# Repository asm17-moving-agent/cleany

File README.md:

# Cleany 로봇 런타임

Cleany 로봇의 ROS 2 runtime, Gazebo/MuJoCo 시뮬레이션, ESP32 펌웨어를 관리하는 저장소입니다. 제품 목표와 설계 결정은 [KB](docs/cleany-docs/README.md)에서 확인합니다. 각 구현과 시험의 상태는 제품 전체의 완료 여부와 구분합니다.

## 문서 지도

```mermaid
flowchart TB
    KB["KB / 제품 목표와 설계 결정"]
    Entry["README / 작업 선택"]
    Setup["DEVELOPMENT_SETUP / 환경과 빌드"]
    Run["RUNNING / 실행"]
    Test["TESTING / 검증"]
    Cal["CALIBRATION / 수집과 평가"]
    Contract["INTEGRATION / 연결과 계약 위치"]
    Ref["코드 옆 docs / 단위와 안전 규약"]
    API["ROS_INTERFACES / 노드별 통신 목록"]
    Evidence["EVIDENCE / 과거 원본 위치"]
    KB -. "제품 기준" .-> Entry
    Entry --> Setup
    Setup --> Run
    Run --> Test
    Run --> Cal
    Entry --> Contract
    Contract --> Ref
    Entry --> API
    API --> Ref
    Test --> Evidence
```

## 개발 시작

기준 환경은 Ubuntu 22.04, ROS 2 Humble, Python 3.10, Gazebo Fortress 6입니다. 새 환경은 [개발환경 설치](docs/DEVELOPMENT_SETUP.md)를 먼저 따릅니다. 아래 명령은 저장소 루트의 Humble 터미널에서 실행합니다.

```bash
git submodule update --init --recursive docs/cleany-docs
source /opt/ros/humble/setup.bash
make deps-gazebo
make test-gazebo
make sim-gazebo
```

전체 workspace는 `make deps`, `make build`, `make test`를 사용합니다. 각 검사의 범위와 시뮬레이션, 실물 검증의 차이는 [테스트 가이드](docs/TESTING.md)에서 확인합니다.

## 필요한 문서

| 작업 | 문서 |
|---|---|
| 환경 설치, 의존성, 빌드 경로 | [개발환경](docs/DEVELOPMENT_SETUP.md) |
| 시뮬레이션, Mission Runtime, Monitor 실행 | [실행](docs/RUNNING.md) |
| 변경 검증, runtime 시험, 결과 저장 | [테스트](docs/TESTING.md) |
| hand-eye 데이터 수집과 검토 | [Calibration](docs/CALIBRATION.md) |
| 노드별 토픽, 서비스, 액션 찾기 | [ROS 인터페이스 색인](docs/ROS_INTERFACES.md) |
| Backend, ROS, MCU 연동 | [연동과 계약](docs/INTEGRATION.md) |
| 펌웨어 빌드, 업로드, 장치 확인 | [ESP32](esp32/README.md), [배선](esp32/PINMAP.md) |
| 과거 보고서와 실행 원본 찾기 | [근거 색인](docs/EVIDENCE.md) |
| 코드 구조와 구현 학습 | [학습 가이드와 HTML 생성 안내](docs/guide/README.md) |
| 인식과 sorting 실행 | [Perception](ros2_ws/src/cleany_perception/docs/runtime.md), [Manipulation](ros2_ws/src/cleany_skill_executor/docs/manipulation.md) |
| 물체 하나의 Action 실행 | [Mock 서버](ros2_ws/src/cleany_skill_executor/docs/manipulation_mock_usage.md), [MuJoCo BT 서버](ros2_ws/src/cleany_manipulation_bt/README.md) |
| 제품, 설계, 미해결 질문 | [KB](docs/cleany-docs/README.md) |

## 코드 위치

| 위치 | 책임 |
|---|---|
| `ros2_ws/src/` | ROS 패키지, 순수 core, launch와 package 설정 |
| `esp32/` | micro-ROS 펌웨어, 빌드 보조 도구, 장치 없는 검사와 PCB |
| `tests/` | 패키지 경계를 넘는 통합 검사 |
| `tools/` | 빌드 출력 정리와 vision 환경 준비 도구 |

생성물과 실행 원본은 기본적으로 worktree 옆 `../cleany-data/`에 둡니다. 사용 가능한 명령은 `make help`, 실제 옵션은 Makefile, launch, config에서 확인합니다. 문서 변경은 기존 설명에 반영하며, README에는 날짜별 구현 일지를 추가하지 않습니다.

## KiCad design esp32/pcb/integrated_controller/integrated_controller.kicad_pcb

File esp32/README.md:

# ESP32-S3 micro-ROS motor controller

Native USB micro-ROS와 encoder, PWM/DIR로 4륜을 제어하는 펌웨어입니다. Target은 ESP32-S3 N32R16V(octal flash 32 MB / PSRAM 16 MB), PlatformIO environment는 `esp32-s3-microros`입니다. GPIO는 [PINMAP](PINMAP.md), 고정 버전은 `micro_ros.lock.json`에서 확인합니다.

| 경로 | 역할 |
|---|---|
| src/ | firmware, motor core |
| host_tests/ | 장치 없는 C++/Python 검사 |
| scripts/ | PlatformIO, 고정 dependency bootstrap |
| microros_smoke/ | micro-ROS/type-support 링크 검사 |
| imu_calibration/ | MPU6050 정지 보정 진단과 USB JSON 결과 |
| pcb/ | KiCad, 로컬 library |
| micro_ros/, .venv/ | 생성 dependency, 빌드 도구 |

도구 이동 후에는 `make firmware-setup`으로 Git wrapper 링크를 갱신합니다. Wrapper는 component root와 하위 폴더 clone 모두 revision을 고정합니다.

## KiCad 보드

[통합 컨트롤러 프로젝트](pcb/integrated_controller/integrated_controller.kicad_pro)는
ESP32-S3 모듈, BNO055, ToF 멀티플렉서와 전원 회로를 포함합니다.
KiCad 10에서 프로젝트를 열고 [보드 핀맵](pcb/integrated_controller/PINMAP.md),
[BOM](pcb/integrated_controller/BOM.md), [제작 규칙](pcb/integrated_controller/DESIGN_RULES.md)을 함께 확인합니다.
검사는 저장소 루트의 `make test-pcb`로 실행하며 환경과 결과 경로는
[개발환경](../docs/DEVELOPMENT_SETUP.md#kicad-pcb-검증-환경)과
[검증 절차](../docs/TESTING.md#통합-컨트롤러-pcb-검증)를 따릅니다.

현재 펌웨어의 모터 GPIO와 MPU6050 드라이버는 기존 모터 보드 기준입니다.
통합 보드에는 모터 GPIO 매핑과 BNO055 드라이버의 별도 이식이 필요합니다.
[별도 USB 센서 캐리어](pcb/sensor_controller/sensor_controller.md)는
회로도와 제작 설정 초안이며 부품 배치와 배선이 없는 상태입니다.

## ROS 인터페이스

노드 이름은 `cleany_motor_controller`, namespace는 기본 root입니다. [main.cpp](src/main.cpp)의 rclc entity 초기화를 기준으로 기록합니다.

| 종류 / 방향 | 기본 이름 | ROS 타입 | QoS와 주기 |
|---|---|---|---|
| 토픽 구독 | `base/wheel_command` | `cleany_base_interfaces/msg/WheelCommand` | Best-effort, volatile, keep-last 1 |
| 토픽 발행 | `base/wheel_state` | `cleany_base_interfaces/msg/WheelState` | Best-effort, volatile, keep-last 1; 50 Hz |
| 토픽 발행 | `base/imu_state` | `cleany_base_interfaces/msg/ImuState` | Best-effort, volatile, keep-last 1; 최대 100 Hz |

MCU에 서비스와 액션은 없습니다. 구동 허가는 WheelCommand의 ENABLE/STOP으로 처리하고, ROS `base/enable` 서비스는 [base driver](../ros2_ws/src/cleany_base_driver/docs/interfaces.md)가 제공합니다. 전체 노드는 [ROS 인터페이스 색인](../docs/ROS_INTERFACES.md)에서 찾습니다.

## Runtime

```mermaid
flowchart TB
    Driver["ROS base driver"] -->|"base/wheel_command"| USB["USB XRCE-DDS"]
    subgraph Communication["통신 task"]
        Callback["rclc callback"] --> Mailbox["최신 명령 mailbox"]
        Ping["Agent ping / 재연결"]
    end
    USB --> Callback
    subgraph Control["motor task / 5 ms"]
        Gate["ENABLE / deadline 검사"] --> PI["PI + feed-forward"] --> PWM["PWM / DIR"]
        Encoder["Encoder feedback"] --> PI
        Encoder --> State["Wheel state"]
    end
    Mailbox --> Gate
    Ping -->|"단절 시 STOP latch"| Gate
    PWM --> Motor["네 휠"]
    Motor --> Encoder
    State -->|"base/wheel_state"| USB
    USB --> Driver
```

통신 task는 USB, ROS entity, Agent 재연결을 관리합니다. Motor task는 독립적으로 5 ms마다 실행하며, `motorMutex` 안에서 명령을 검사하고 PWM을 갱신합니다. 부팅 시 PWM은 0이고 구동은 disabled입니다. Zero ENABLE을 받은 뒤 VELOCITY를 허용합니다.

| 조건 | 처리 |
|---|---|
| STOP, 재연결 | Sequence high-water 유지 |
| 거부된 명령, 반복 ENABLE | Deadline과 이동 목표를 갱신하지 않음 |
| STOP latch | 대기 명령 삭제; 새 sequence로 오래된 ENABLE 차단 |
| Deadline | 수신 후 최대 250 ms; 명령 처리 전에 검사 |
| 만료, 단절 | 허가 해제; 재개에는 새 ENABLE 필요 |
| STOP, 만료, 단절 | Controller reset과 PWM 0 요청 |
| Agent ping 실패 | STOP latch → entity teardown → 재연결 |

| 항목 | 값과 규칙 |
|---|---|
| Wheel ceiling, 목표 반올림 | 10 rad/s, 0.1 rad/s 단위 |
| PWM | 20 kHz, 명령 슬루는 20 ms당 가속 1%p, 감속 3%p |
| 방향 반전 | 측정 속도 ≤0.5 rad/s를 50 ms 유지한 뒤 DIR 변경 |
| Wheel 배열 | FL/FR/RL/RR → PCB M1/M2/M4/M3, mapping `{0,1,3,2}` |
| 극성, encoder | 극성은 MCU에서만 적용; 출력축 1회전=3172 counts |
| State | 50 Hz, best-effort/volatile/keep-last-1 |
| MCU 시간, Boot ID | Monotonic µs; reboot baseline 식별 |
| USB | Agent용 framed XRCE-DDS 전용 |
| Agent ping | 100 ms 주기, 20 ms timeout |

메시지와 명령 수락 규칙은 [protocol v2](../ros2_ws/src/cleany_base_interfaces/docs/protocol.md)를 따릅니다.

## Runtime MPU6050 telemetry

The motor image also acquires MPU6050 data on J_I2C1 (SDA GPIO41, SCL GPIO42),
using the existing driver: 100 kHz I2C, 100 Hz sensor sampling, ±250 deg/s gyro,
±2 g accelerometer and 42 Hz gyro DLPF. Module/external I2C pull-ups are required.

The independent priority-2 acquisition task polls data-ready every 2 ms. It does
not take `motorMutex`. The priority-6 motor and priority-4 communication tasks
remain separate. A one-entry overwrite queue drops intermediate data if
communication stalls; reconnect does not drain a sample backlog.

The communication task publishes fixed-size `ImuState` on `base/imu_state`,
best effort / volatile / keep last 1, driven by newly acquired samples up to
the sensor rate. WheelState remains at 50 Hz. Actual rates and motor timing
under combined USB/I2C load require robot measurements.

Packets carry uncalibrated sensor-frame SI vectors, temperature, MCU MAC,
WHO_AM_I, boot ID, packet sequence, MCU acquisition timestamp and fault bits.
ImuState v2 also carries MCU-corrected gyro, the selected bias/covariance,
and calibration state/reason. Build the ROS interfaces and firmware together.
Acquisitions older than 100 ms and duplicate/backward timestamps are not sent
as new measurements. Missing/error data produces a sensor-fault heartbeat
at most 10 Hz; saturation has its own fault bit. Initialization/read errors
retry with 250 ms to 5 s backoff. IMU I2C failure does not authorize motors.

### Power-on calibration

The acquisition task calibrates once per MCU boot, independently of the Agent.
Defaults are 5 s settling, 1,000 training samples and 500 holdout samples, with
a 25 s deadline. It reuses the existing online gyro statistics. Noise/residual
failure, sensor/sample errors or timeout select the saved bench coefficients.
The selection remains fixed until MCU reboot, including across Agent reconnects.

During calibration, motor PWM stays zero, PID updates are skipped and non-STOP
commands are discarded. Completion only releases this inhibit; a fresh ENABLE
is still required. STOP, watchdog and disconnect handling remain active.
Fallback can release the calibration inhibit even if the sensor is unavailable;
sensor errors are still reported, and no angular-rate samples are fabricated.

Edit [`ros2_ws/src/cleany_base_driver/config/imu_calibration.json`](../ros2_ws/src/cleany_base_driver/config/imu_calibration.json)
to configure timing, windows, checks and measured fallback bias/covariance.
`make firmware-build` validates it and generates `cleany_config/imu_startup_config.hpp`
inside the PlatformIO build directory. The configuration is compiled into the
image; changes require rebuilding and uploading. Runtime checks samples and
observed statistics. A single acquisition-side enqueue helper attaches calibration
metadata and releases the boot inhibit on completion. The IMU task uses 6144 bytes
of stack for online statistics.

ROS topics and status are documented under
[IMU 실시간 수신](../ros2_ws/src/cleany_base_driver/docs/imu.md#imu-실시간-수신).
The standalone [diagnostic](imu_calibration/README.md) provides bench reports;
normal startup calibration is part of the motor image.

## 휠별 초기 PI와 FF

`src/main.cpp`의 `kFl/Fr/Rl/RrControllerConfig`에서 FF scale / Kp / Ki / PWM limit 순서로 설정합니다. 변경 후 rebuild와 upload가 필요합니다. FF 출력은 `target / FF scale × PWM limit`입니다.

아래 값은 2026-10-02 네 바퀴를 공중에 띄운 무부하 시험에서 얻었습니다. PI를 끄고 네 휠을 동시에 정, 역방향으로 PWM 0→100%, 5% 간격, 1.5초씩 측정했습니다.

| 휠 | FF scale (rad/s) | Kp | Ki | PWM 상한 (%) |
|---|---:|---:|---:|---:|
| FL | 12.4261 | 4.655 | 9.309 | 100 |
| FR | 12.1178 | 4.711 | 9.421 | 100 |
| RL | 11.6403 | 4.864 | 9.728 | 100 |
| RR | 11.8128 | 4.783 | 9.566 | 100 |

FF는 `PWM≈k×속도`, `FF scale=100/k`로 추정하고 마찰 잔차는 PI로 보정했습니다. PI 추정에는 gain K, 시정수 τ, delay L과 기존 50 ms 속도 필터를 포함했습니다. 계산식은 `Kp=clamp(0.6/K,2,8)`, `Ki=Kp/max(0.5,4(τ+L))`입니다.

보정값을 업로드한 뒤 네 바퀴 동시 정·역방향 **0.5, 2, 5, 10 rad/s** 명령을
각각 5초 동안 검증했다. 마지막 0.5초 평균 속도 오차는 모든 휠에서 4.5% 이내였다.
최종 상태는 구동 비허가, PWM 0, fault 0이다.

### 2026-10-13 지면 하중 실측 캘리브레이션 및 필터 고도화

현재 `src/main.cpp`는 전후이동과 횡이동의 지면 하중 시험에서 도출한 다음
휠별 설정을 사용한다. 진단 기준값은
[`controller_baseline.json`](../tools/wheel_calibration/controller_baseline.json)에
같은 값으로 보존하며, 관련 테스트가 펌웨어 설정과의 일치를 확인한다.

| 휠 | FF scale (rad/s) | Kp | Ki | PWM 상한 (%) | 주요 지면 보정 특성 |
|---|---:|---:|---:|---:|---|
| FL | 11.9352 | 6.058 | 12.118 | 100 | 전후/횡이동 균형 최적화 |
| FR | 12.2596 | 6.030 | 12.058 | 100 | 고효율 FR 휠 출력 과다 방지 |
| RL | 11.7678 | 6.246 | 12.492 | 100 | 후륜 지지 강성 보강 |
| RR | 11.3872 | 6.154 | 12.309 | 100 | 기어박스 마찰 하중 보상 (Yaw 편주 억제) |

명령 슬루는 가속 시 20 ms당 1%, 감속 시 20 ms당 3%로 설정한다.
속도 피드백 LPF 시상수는 `kVelocityFilterTimeConstantSeconds = 0.02`초다.
STOP, 만료 및 연결 단절은 슬루 감속을 기다리지 않고 PWM zero를 요청한다.

측정과 재검증 방법은 [휠 진단 안내](../tools/wheel_calibration/README.md)와
[오도메트리 평가 안내](../tools/odometry_evaluation/README.md)를 따른다.
오도메트리 내부 제어 잔차와 바닥 테이프 또는 LiDAR 기준의 실측 오차는
별도 지표로 기록한다. 측정 JSON과 PNG는 Git 제외 경로인 `artifacts/`에 저장한다.

## 1. 빌드와 장치 없는 검사

명령은 저장소 루트에서 실행합니다. 호스트 호출 시 Ubuntu 22.04 `ros2-humble` Distrobox를 사용합니다.

```bash
make firmware-setup
make test-micro-ros-setup test-motor-core
make firmware-smoke
make firmware-build
make build-base test-base
make micro-ros-agent-build
```

Type support 원본은 `ros2_ws/src/cleany_base_interfaces`입니다. Smoke/runtime은 cache를 공유하므로 순차 빌드하며, interface, metadata, 환경을 변경하면 type support를 재생성합니다.

`cmake/microros_python.cmake` exposes the pinned generator modules to IDF's
Python during CMake configuration. PlatformIO clears the process `PYTHONPATH`
before this step, so the SCons environment alone does not cover a fresh
micro-ROS/type-support rebuild. Runtime and smoke projects share this helper.

Smoke and runtime share a library cache and build sequentially. Changes to
interfaces, metadata, or build environment regenerate type support.
`sdkconfig.defaults` configures octal memory, a 1000 Hz FreeRTOS tick, and the
USB transport. The DOUT image header lets the bootloader enable OPI.

For clangd, run inside Distrobox:

```bash
esp32/.venv/bin/platformio run -d esp32 -e esp32-s3-microros -t compiledb
```

## 2. Upload와 통신

For stationary gyro calibration on `J_I2C1`, use the separate
[MPU6050 calibration diagnostic](imu_calibration/README.md).
It provides a calibration-only image, retained USB results, measured-limit
configuration, and the motor-firmware restoration procedure.

Select the device and confirm upload:

```bash
make firmware-upload CLEANY_ESP_PORT=/dev/serial/by-id/<device> CONFIRM_UPLOAD=1
```

Agent/ROS overlay를 적용하고 DDS domain 0에서 통신을 확인합니다.

```bash
source /opt/ros/humble/setup.bash
source esp32/micro_ros/agent/install/local_setup.bash
source "$(make -s print-install-base)/local_setup.bash"
export ROS_DOMAIN_ID=0
ros2 run micro_ros_agent micro_ros_agent serial --dev "$CLEANY_ESP_PORT" -b 115200
# Another terminal with the same overlays/domain:
ros2 topic echo /base/wheel_state --qos-reliability best_effort
```

Bare MCU 확인 항목은 다음과 같습니다.

- Nonzero boot ID, 증가하는 sequence/timestamp
- Disabled 상태, 목표, PWM 0, fault 없음

## 3. 실물 인수

1. 감독자, 사람 없는 구역, 검토한 제한값, 접근 가능한 물리 E-stop을 준비합니다.
2. 바퀴를 띄워 startup 0, 회전 방향, encoder 부호를 확인합니다.
3. Enable 후 새 저속 명령으로 전진, 좌측, yaw, PI, PWM slew, 반전 dwell을 확인합니다.
4. STOP, 만료, driver/Agent 종료, USB 단절, MCU reboot의 정지 시간을 측정합니다.
5. 재연결 후 새 enable과 새 명령이 필요한지 확인합니다.

Odometry, TF 소유권은 [Base 계약](../ros2_ws/src/cleany_base_driver/docs/command-and-odometry.md)을 따릅니다. 결과에는 revision, 설정, 하중/바닥, 부호, 주기, 정지 시간을 기록합니다.

## KiCad

프로젝트는 [motor_controller.kicad_pro](pcb/motor_controller.kicad_pro)이며 symbol/footprint는 project-local table에 등록됩니다. Espressif 출처와 라이선스는 [libraries](pcb/libraries/README.md)에서 확인합니다.

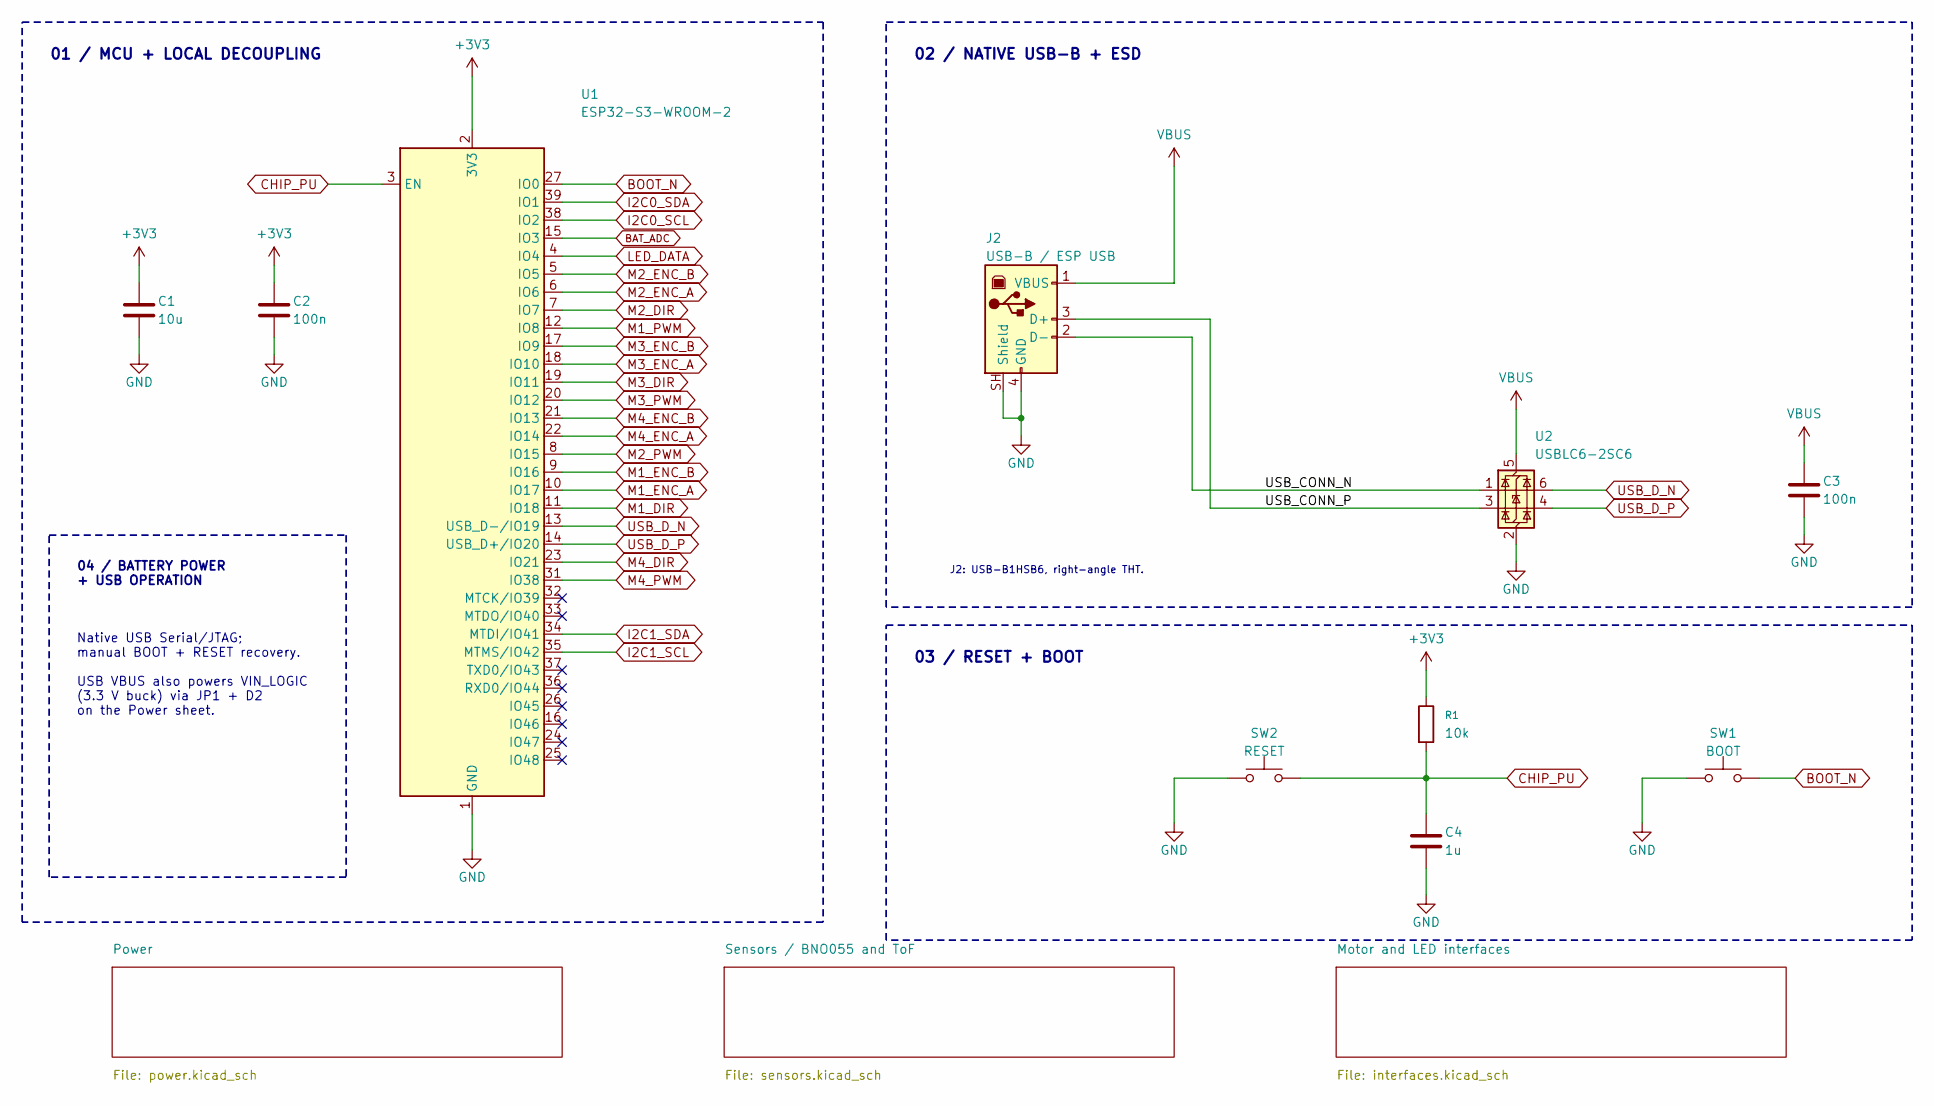
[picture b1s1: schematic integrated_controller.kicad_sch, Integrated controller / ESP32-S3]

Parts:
C1: 10u; C_0805_2012Metric; Tolerance 10%; Voltage 25V; MPN C2012X5R1E106K125DB
C2, C3: 100n; C_0603_1608Metric; Tolerance 10%; Voltage 50V; MPN C0603C104K5RACTU
C4: 1u; C_0603_1608Metric; Tolerance 10%; Voltage 16V; MPN C0603C105K4RACTU
J2: USB-B / ESP USB; USB_B_OST_USB-B1HSxx_Horizontal; MPN USB-B1HSB6
R1: 10k; R_0603_1608Metric; Tolerance 1%; MPN ERJ-3EKF1002V
SW1: BOOT; SW_SPST_PTS810; MPN PTS810SJM250SMTR LFS
SW2: RESET; SW_SPST_PTS810; MPN PTS810SJM250SMTR LFS
U1: ESP32-S3-WROOM-2; MPN ESP32-S3-WROOM-2-N32R16V
U2: USBLC6-2SC6; SOT-23-6; MPN USBLC6-2SC6

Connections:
+3V3: C1.1, C2.1, R1.1, U1.2 (3V3); also elsewhere on the board
/USB_CONN_N: J2.2 (D-), U2.1 (I/O1)
/USB_CONN_P: J2.3 (D+), U2.3 (I/O2)
BAT_ADC: U1.15 (IO3); also elsewhere on the board
BOOT_N: SW1.2, U1.27 (IO0)
CHIP_PU: C4.1, R1.2, SW2.2, U1.3 (EN)
GND: C1.2, C2.2, C3.2, C4.2, J2.4 (GND), J2.SH (Shield), SW1.1, SW2.1, U1.1 (GND), U1.40 (GND), U1.41 (GND), U2.2 (GND); also elsewhere on the board
I2C0_SCL: U1.38 (IO2); also elsewhere on the board
I2C0_SDA: U1.39 (IO1); also elsewhere on the board
I2C1_SCL: U1.35 (MTMS/IO42); also elsewhere on the board
I2C1_SDA: U1.34 (MTDI/IO41); also elsewhere on the board
LED_DATA: U1.4 (IO4); also elsewhere on the board
M1_DIR: U1.11 (IO18); also elsewhere on the board
M1_ENC_A: U1.10 (IO17); also elsewhere on the board
M1_ENC_B: U1.9 (IO16); also elsewhere on the board
M1_PWM: U1.12 (IO8); also elsewhere on the board
M2_DIR: U1.7 (IO7); also elsewhere on the board
M2_ENC_A: U1.6 (IO6); also elsewhere on the board
M2_ENC_B: U1.5 (IO5); also elsewhere on the board
M2_PWM: U1.8 (IO15); also elsewhere on the board
M3_DIR: U1.19 (IO11); also elsewhere on the board
M3_ENC_A: U1.18 (IO10); also elsewhere on the board
M3_ENC_B: U1.17 (IO9); also elsewhere on the board
M3_PWM: U1.20 (IO12); also elsewhere on the board
M4_DIR: U1.23 (IO21); also elsewhere on the board
M4_ENC_A: U1.22 (IO14); also elsewhere on the board
M4_ENC_B: U1.21 (IO13); also elsewhere on the board
M4_PWM: U1.31 (IO38); also elsewhere on the board
USB_D_N: U1.13 (USB_D-/IO19), U2.6 (I/O1)
USB_D_P: U1.14 (USB_D+/IO20), U2.4 (I/O2)
VBUS: C3.1, J2.1 (VBUS), U2.5 (VBUS); also elsewhere on the board

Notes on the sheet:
04 / BATTERY POWER + USB OPERATION
Native USB Serial/JTAG; manual BOOT + RESET recovery. USB VBUS also powers VIN_LOGIC (3.3 V buck) via JP1 + D2 on the Power sheet.
J2: USB-B1HSB6, right-angle THT.
02 / NATIVE USB-B + ESD
01 / MCU + LOCAL DECOUPLING
03 / RESET + BOOT

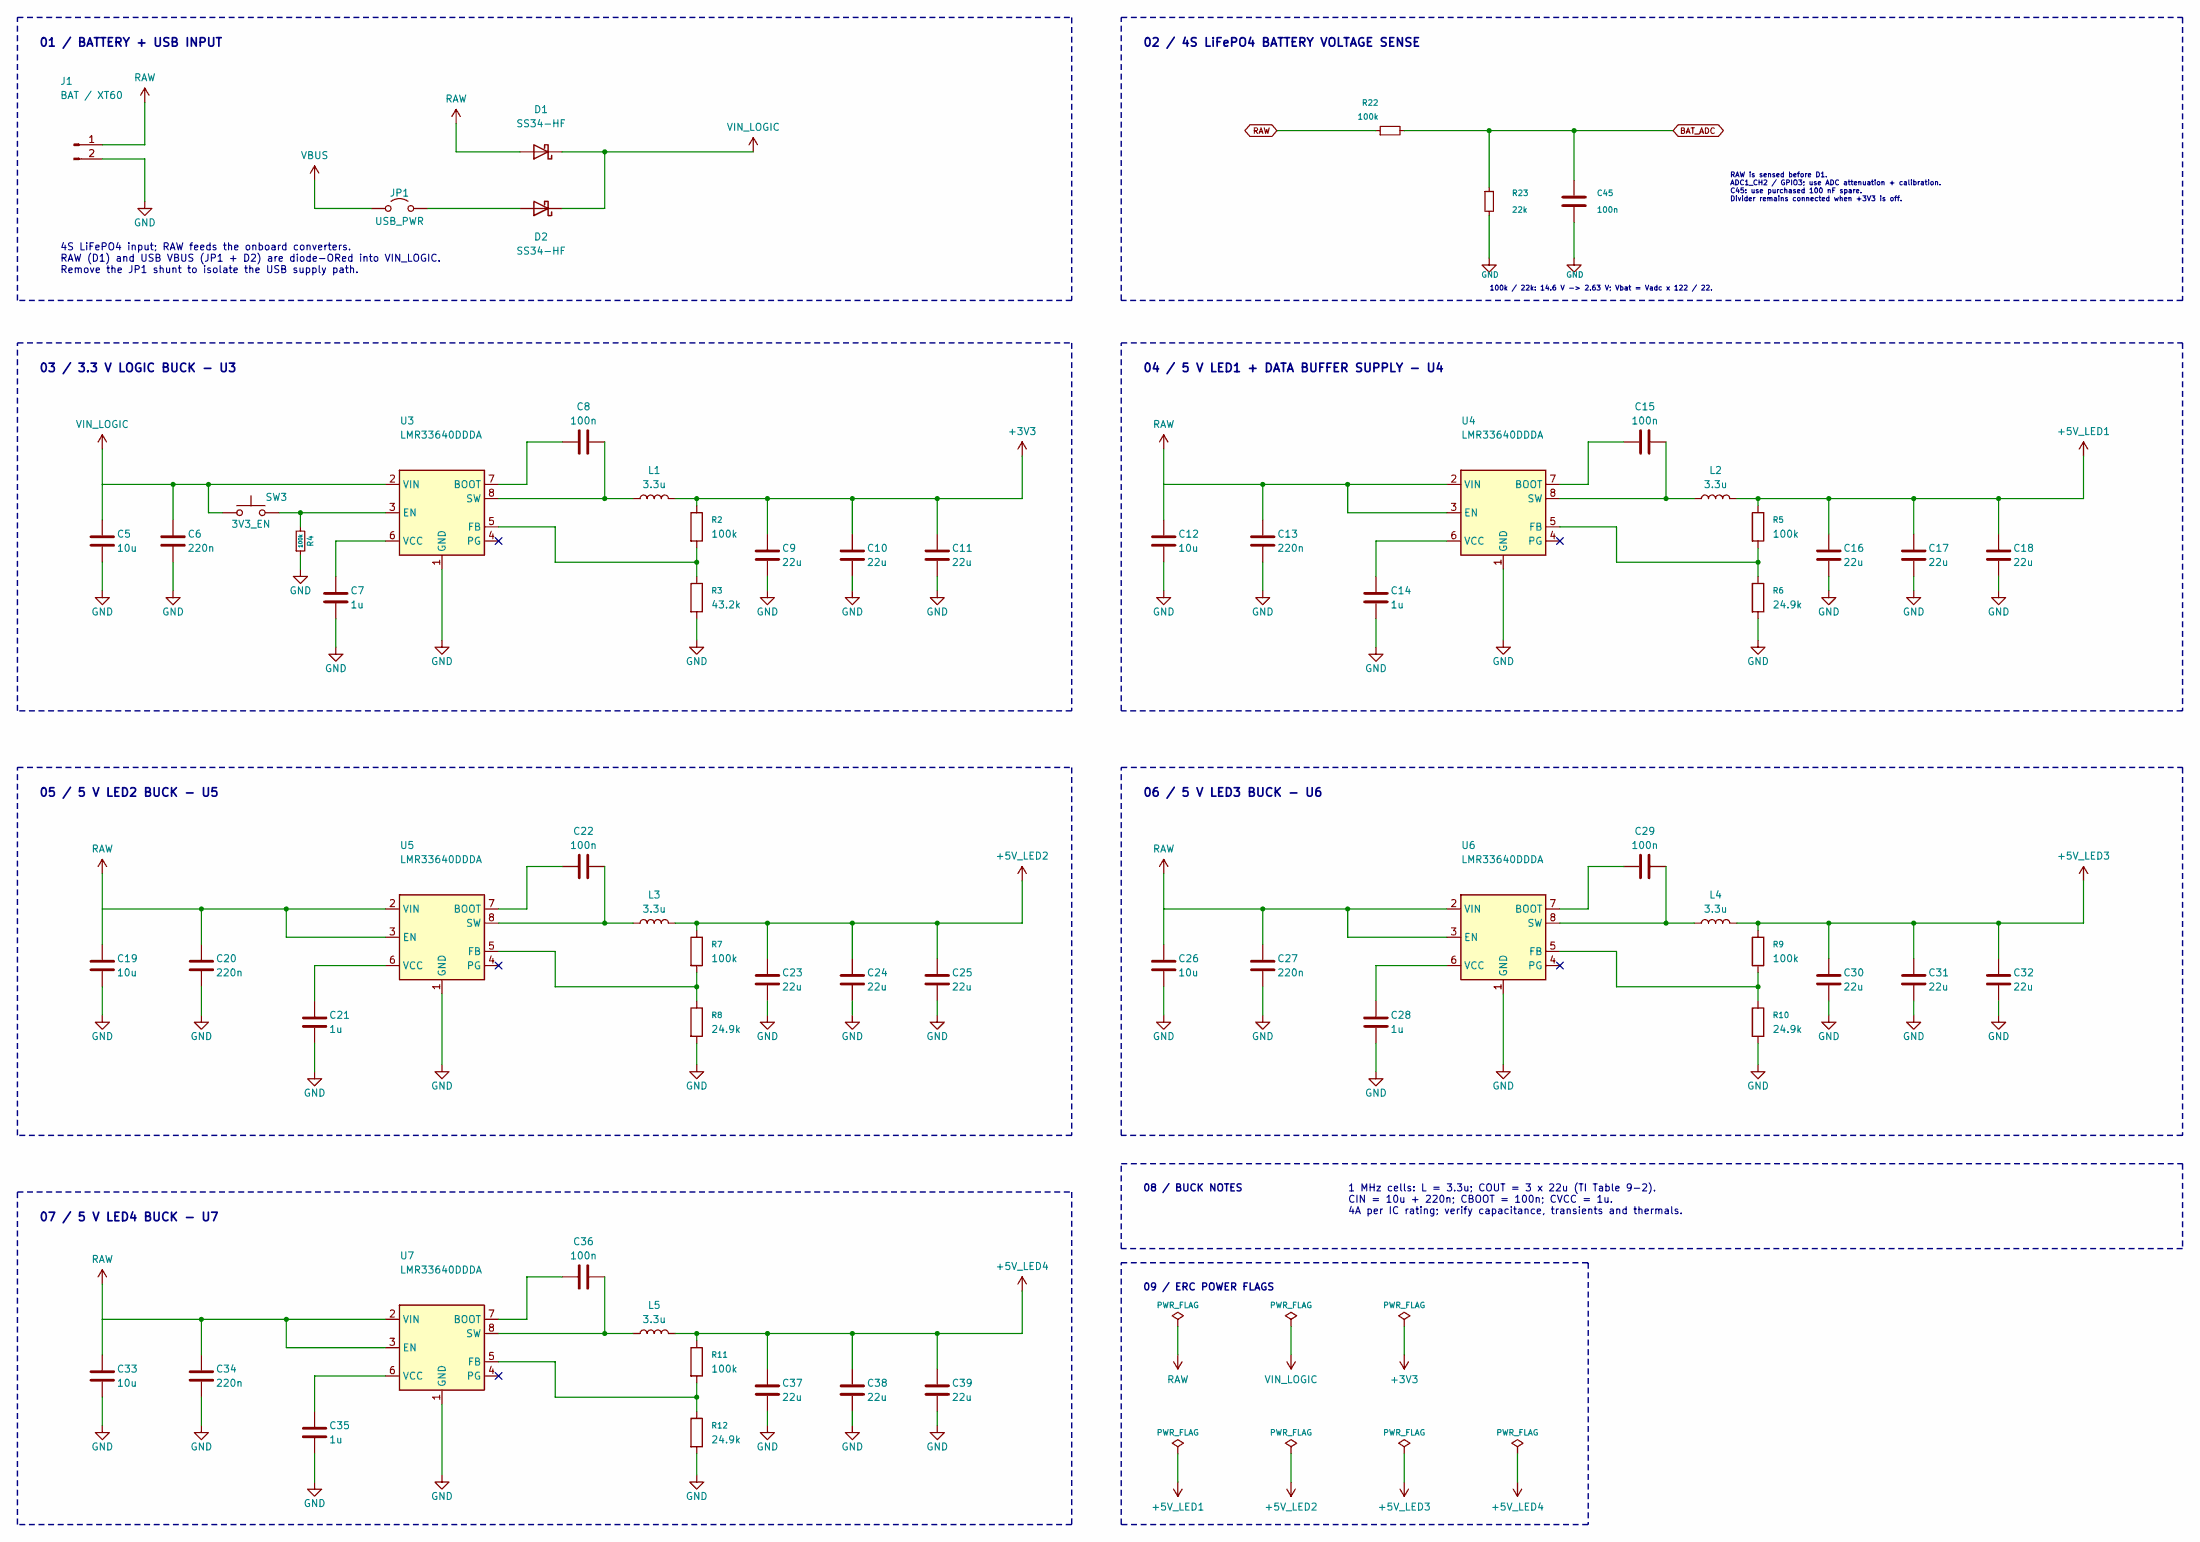
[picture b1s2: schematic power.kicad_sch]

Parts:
C5, C12, C19, C26, C33: 10u; C_1206_3216Metric; Voltage 50V; Tolerance 10%; MPN GMC31X5R106K50NT
C6, C13, C20, C27, C34: 220n; C_0603_1608Metric; Voltage 50V; Tolerance 10%; MPN GRM188R71H224KAC4D
C7, C14, C21, C28, C35: 1u; C_0603_1608Metric; Voltage 16V; Tolerance 20%; MPN CL10B105MO8NNWC
C8, C15, C22, C29, C36: 100n; C_0603_1608Metric; Voltage 25V; Tolerance 10%; MPN KGM15BR71E104KT
C9, C10, C11, C16, C17, C18, C23, C24, C25, C30, C31, C32, C37, C38, C39: 22u; C_1210_3225Metric; Voltage 16V; Tolerance 20%; MPN CGA6P1X7R1C226M250AC
C45: 100n; C_0603_1608Metric; MPN C0603C104K5RACTU
D1, D2: SS34-HF; D_SMA; MPN SS34-HF
J1: BAT / XT60; XT60_Generic_Vertical_1x02_P7.20mm_Pin1Positive
JP1: USB_PWR; PinHeader_1x02_P2.54mm_Vertical; MPN PREC002SAAN-RC
L1, L2, L3, L4, L5: 3.3u; Wuerth_74439346033_6.65x6.45mm; Tolerance 20%; MPN 74439346033
R2, R5, R7, R9, R11: 100k; R_0603_1608Metric; Tolerance 1%; MPN CRCW0603100KFKEA
R3: 43.2k; R_0603_1608Metric; Tolerance 1%; MPN ERJ-3EKF4322V
R4: 100k; R_0603_1608Metric
R6, R8, R10, R12: 24.9k; R_0603_1608Metric; Tolerance 1%; MPN RC0603FR-0724K9L
R22: 100k; R_0603_1608Metric; MPN CRCW0603100KFKEA
R23: 22k; R_0603_1608Metric; MPN CRCW060322K0FKEA
SW3: 3V3_EN; Molex_SPOX_5268-02A_1x02_P2.50mm_Horizontal
U3, U4, U5, U6, U7: LMR33640DDDA; Texas_HSOP-8-1EP_3.9x4.9mm_P1.27mm_ThermalVias; MPN LMR33640DDDAR

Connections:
+3V3: C9.1, C10.1, C11.1, L1.2, R2.1; also elsewhere on the board
+5V_LED1: C16.1, C17.1, C18.1, L2.2, R5.1; also elsewhere on the board
+5V_LED2: C23.1, C24.1, C25.1, L3.2, R7.1; also elsewhere on the board
+5V_LED3: C30.1, C31.1, C32.1, L4.2, R9.1; also elsewhere on the board
+5V_LED4: C37.1, C38.1, C39.1, L5.2, R11.1; also elsewhere on the board
BAT_ADC: C45.1, R22.2, R23.1; also elsewhere on the board
GND: C5.2, C6.2, C7.2, C9.2, C10.2, C11.2, C12.2, C13.2, C14.2, C16.2, C17.2, C18.2, C19.2, C20.2, C21.2, C23.2, C24.2, C25.2, C26.2, C27.2, C28.2, C30.2, C31.2, C32.2, C33.2, C34.2, C35.2, C37.2, C38.2, C39.2, C45.2, J1.2, R3.2, R4.1, R6.2, R8.2, R10.2, R12.2, R23.2, U3.1 (GND), U3.9 (GND), U4.1 (GND), U4.9 (GND), U5.1 (GND), U5.9 (GND), U6.1 (GND), U6.9 (GND), U7.1 (GND), U7.9 (GND); also elsewhere on the board
unnamed: D2.2 (A), JP1.2 (B)
unnamed: C8.1, U3.7 (BOOT)
unnamed: R4.2, SW3.2, U3.3 (EN)
unnamed: R2.2, R3.1, U3.5 (FB)
unnamed: C8.2, L1.1, U3.8 (SW)
unnamed: C7.1, U3.6 (VCC)
unnamed: C15.1, U4.7 (BOOT)
unnamed: R5.2, R6.1, U4.5 (FB)
unnamed: C15.2, L2.1, U4.8 (SW)
unnamed: C14.1, U4.6 (VCC)
unnamed: C22.1, U5.7 (BOOT)
unnamed: R7.2, R8.1, U5.5 (FB)
unnamed: C22.2, L3.1, U5.8 (SW)
unnamed: C21.1, U5.6 (VCC)
unnamed: C29.1, U6.7 (BOOT)
unnamed: R9.2, R10.1, U6.5 (FB)
unnamed: C29.2, L4.1, U6.8 (SW)
unnamed: C28.1, U6.6 (VCC)
unnamed: C36.1, U7.7 (BOOT)
unnamed: R11.2, R12.1, U7.5 (FB)
unnamed: C36.2, L5.1, U7.8 (SW)
unnamed: C35.1, U7.6 (VCC)
RAW: C12.1, C13.1, C19.1, C20.1, C26.1, C27.1, C33.1, C34.1, D1.2 (A), J1.1, R22.1, U4.2 (VIN), U4.3 (EN), U5.2 (VIN), U5.3 (EN), U6.2 (VIN), U6.3 (EN), U7.2 (VIN), U7.3 (EN)
VBUS: JP1.1 (A); also elsewhere on the board
VIN_LOGIC: C5.1, C6.1, D1.1 (K), D2.1 (K), SW3.1, U3.2 (VIN)

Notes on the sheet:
4S LiFePO4 input; RAW feeds the onboard converters. RAW (D1) and USB VBUS (JP1 + D2) are diode-ORed into VIN_LOGIC. Remove the JP1 shunt to isolate the USB supply path.
03 / 3.3 V LOGIC BUCK - U3
09 / ERC POWER FLAGS
07 / 5 V LED4 BUCK - U7
06 / 5 V LED3 BUCK - U6
04 / 5 V LED1 + DATA BUFFER SUPPLY - U4
08 / BUCK NOTES
05 / 5 V LED2 BUCK - U5
1 MHz cells: L = 3.3u; COUT = 3 x 22u (TI Table 9-2). CIN = 10u + 220n; CBOOT = 100n; CVCC = 1u. 4A per IC rating; verify capacitance, transients and thermals.
01 / BATTERY + USB INPUT
02 / 4S LiFePO4 BATTERY VOLTAGE SENSE
RAW is sensed before D1. ADC1_CH2 / GPIO3; use ADC attenuation + calibration. C45: use purchased 100 nF spare. Divider remains connected when +3V3 is off.
100k / 22k: 14.6 V -> 2.63 V; Vbat = Vadc x 122 / 22.

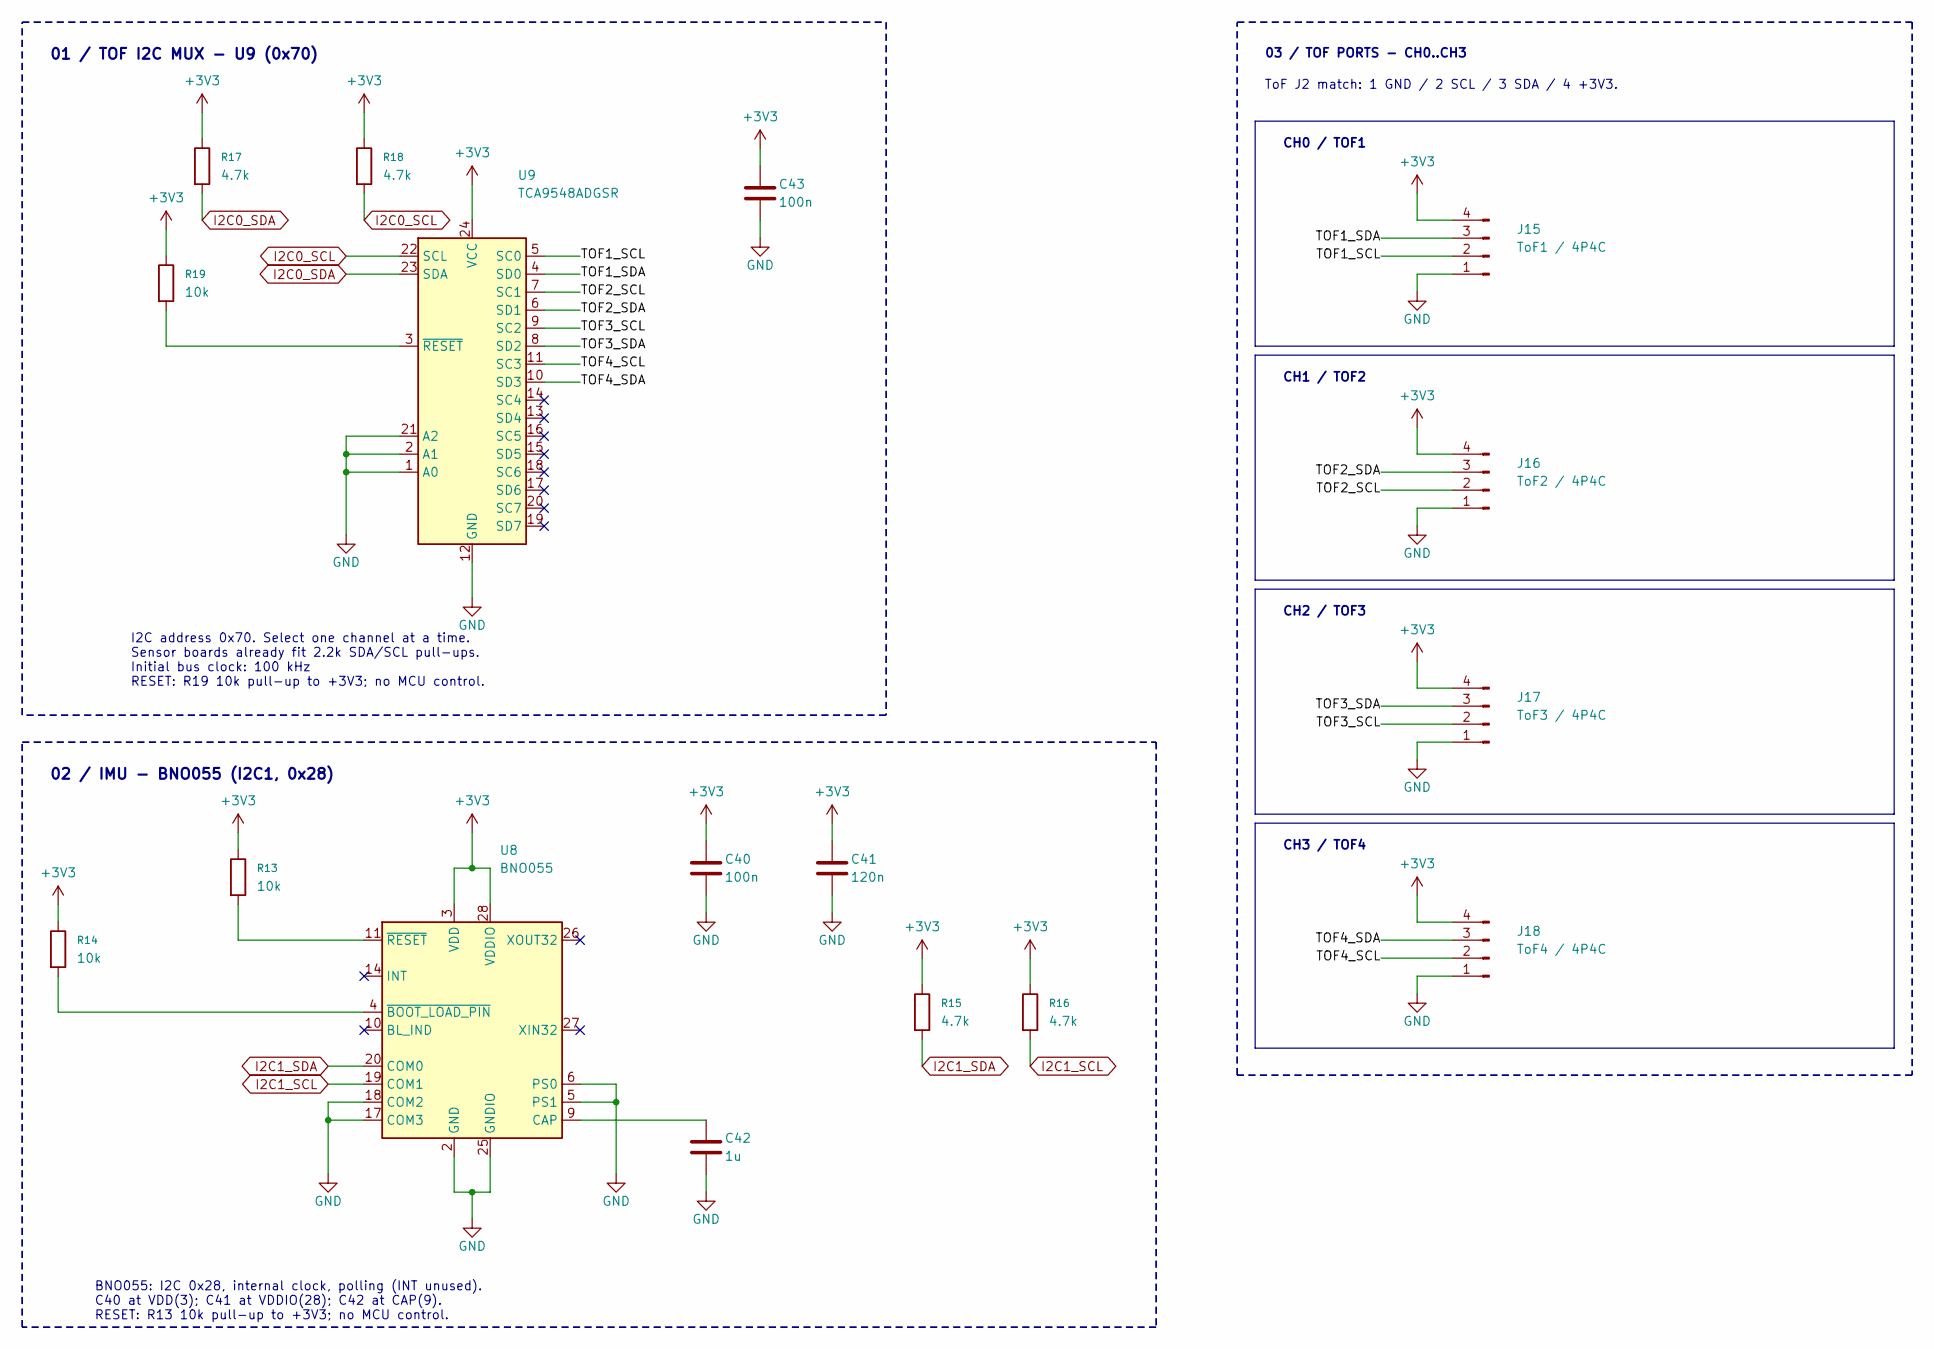
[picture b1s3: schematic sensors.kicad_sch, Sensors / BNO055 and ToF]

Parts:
C40, C43: 100n; C_0603_1608Metric; Voltage 50V; Tolerance 10%; MPN C0603C104K5RACTU
C41: 120n; C_0603_1608Metric; Voltage 50V; Tolerance 10%; MPN C0603C124K5RACTU
C42: 1u; C_0603_1608Metric; Voltage 16V; Tolerance 10%; MPN C0603C105K4RACTU
J15: ToF1 / 4P4C; RJ9_Assmann_A-2004-3-4-LP-N-R_Horizontal; MPN A-2004-3-4-LP-N-R
J16: ToF2 / 4P4C; RJ9_Assmann_A-2004-3-4-LP-N-R_Horizontal; MPN A-2004-3-4-LP-N-R
J17: ToF3 / 4P4C; RJ9_Assmann_A-2004-3-4-LP-N-R_Horizontal; MPN A-2004-3-4-LP-N-R
J18: ToF4 / 4P4C; RJ9_Assmann_A-2004-3-4-LP-N-R_Horizontal; MPN A-2004-3-4-LP-N-R
R13, R14, R19: 10k; R_0603_1608Metric; Tolerance 1%; MPN ERJ-3EKF1002V
R15, R16, R17, R18: 4.7k; R_0603_1608Metric; Tolerance 1%; MPN RC0603FR-074K7L
U8: BNO055; LGA-28_5.2x3.8mm_P0.5mm; MPN BNO055
U9: TCA9548ADGSR; Texas_DGS0024A_VSSOP-24_3x6.1mm_P0.5mm; MPN TCA9548ADGSR

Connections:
+3V3: C40.1, C41.1, C43.1, J15.4, J16.4, J17.4, J18.4, R13.1, R14.1, R15.1, R16.1, R17.1, R18.1, R19.1, U8.3 (VDD), U8.28 (VDDIO), U9.24 (VCC); also elsewhere on the board
/Sensors / BNO055 and ToF/TOF1_SCL: J15.2, U9.5 (SC0)
/Sensors / BNO055 and ToF/TOF1_SDA: J15.3, U9.4 (SD0)
/Sensors / BNO055 and ToF/TOF2_SCL: J16.2, U9.7 (SC1)
/Sensors / BNO055 and ToF/TOF2_SDA: J16.3, U9.6 (SD1)
/Sensors / BNO055 and ToF/TOF3_SCL: J17.2, U9.9 (SC2)
/Sensors / BNO055 and ToF/TOF3_SDA: J17.3, U9.8 (SD2)
/Sensors / BNO055 and ToF/TOF4_SCL: J18.2, U9.11 (SC3)
/Sensors / BNO055 and ToF/TOF4_SDA: J18.3, U9.10 (SD3)
GND: C40.2, C41.2, C42.2, C43.2, J15.1, J16.1, J17.1, J18.1, U8.2 (GND), U8.5 (PS1), U8.6 (PS0), U8.17 (COM3), U8.18 (COM2), U8.25 (GNDIO), U9.1 (A0), U9.2 (A1), U9.12 (GND), U9.21 (A2); also elsewhere on the board
I2C0_SCL: R18.2, U9.22 (SCL); also elsewhere on the board
I2C0_SDA: R17.2, U9.23 (SDA); also elsewhere on the board
I2C1_SCL: R16.2, U8.19 (COM1); also elsewhere on the board
I2C1_SDA: R15.2, U8.20 (COM0); also elsewhere on the board
unnamed: C42.1, U8.9 (CAP)
unnamed: R14.2, U8.4 (~BOOT_LOAD_PIN)
unnamed: R13.2, U8.11 (~RESET)
unnamed: R19.2, U9.3 (~RESET)

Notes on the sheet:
03 / TOF PORTS - CH0..CH3
CH2 / TOF3
CH1 / TOF2
CH0 / TOF1
BNO055: I2C 0x28, internal clock, polling (INT unused). C40 at VDD(3); C41 at VDDIO(28); C42 at CAP(9). RESET: R13 10k pull-up to +3V3; no MCU control.
01 / TOF I2C MUX - U9 (0x70)
CH3 / TOF4
02 / IMU - BNO055 (I2C1, 0x28)
ToF J2 match: 1 GND / 2 SCL / 3 SDA / 4 +3V3.
I2C address 0x70. Select one channel at a time. Sensor boards already fit 2.2k SDA/SCL pull-ups. Initial bus clock: 100 kHz RESET: R19 10k pull-up to +3V3; no MCU control.

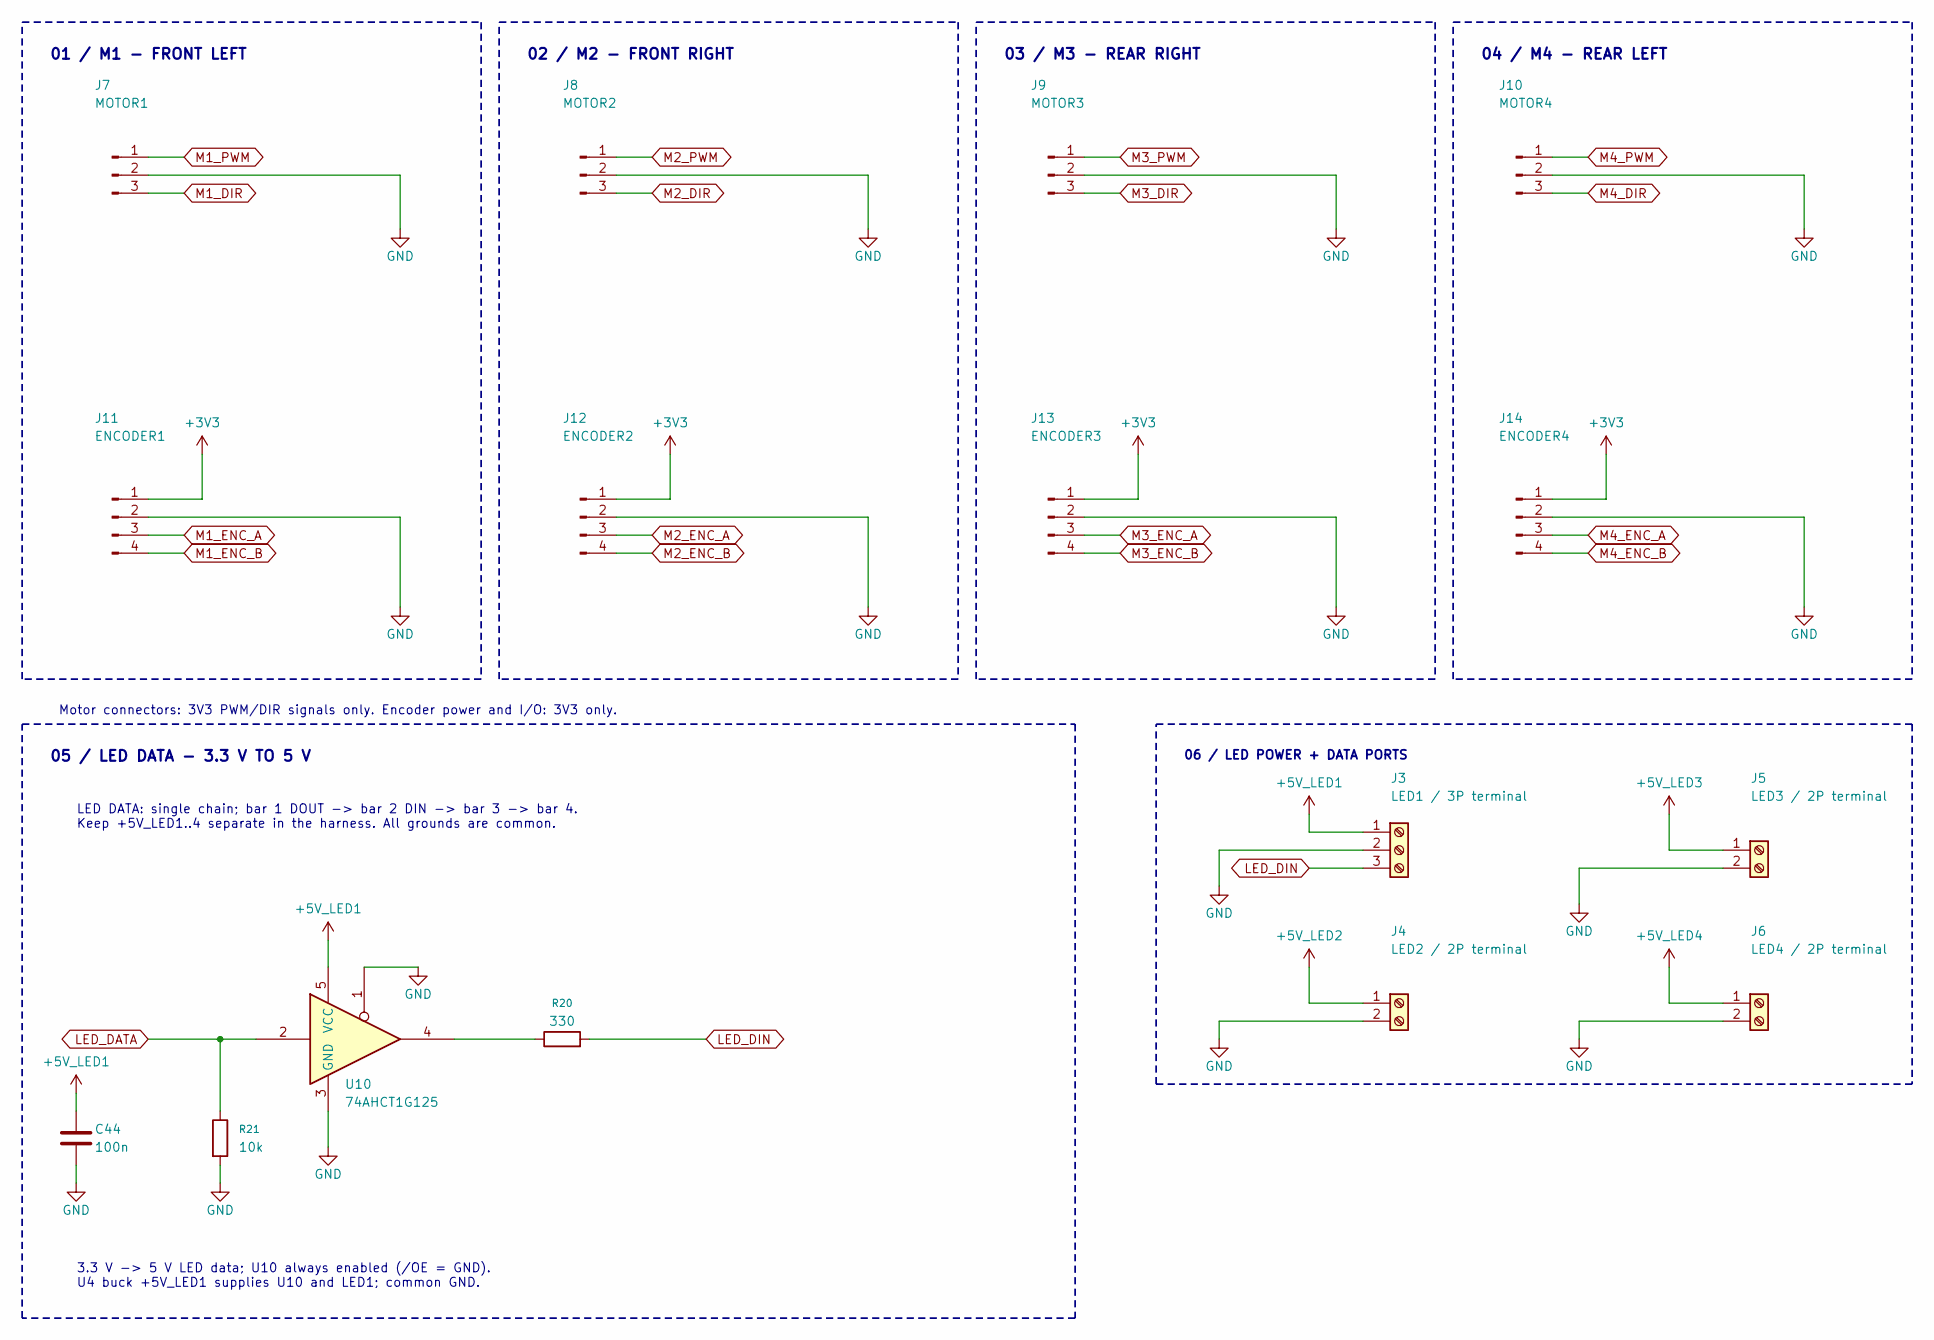
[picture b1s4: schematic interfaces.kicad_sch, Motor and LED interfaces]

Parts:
C44: 100n; C_0603_1608Metric; Voltage 50V; Tolerance 10%; MPN C0603C104K5RACTU
J3: LED1 / 3P terminal; TerminalBlock_Phoenix_PT-1,5-3-5.0-H_1x03_P5.00mm_Horizontal; MPN 1989450
J4: LED2 / 2P terminal; TerminalBlock_Phoenix_PT-1,5-2-5.0-H_1x02_P5.00mm_Horizontal; MPN 1935161
J5: LED3 / 2P terminal; TerminalBlock_Phoenix_PT-1,5-2-5.0-H_1x02_P5.00mm_Horizontal; MPN 1935161
J6: LED4 / 2P terminal; TerminalBlock_Phoenix_PT-1,5-2-5.0-H_1x02_P5.00mm_Horizontal; MPN 1935161
J7: MOTOR1; Molex_SPOX_5268-03A_1x03_P2.50mm_Horizontal; MPN 0022057035
J8: MOTOR2; Molex_SPOX_5268-03A_1x03_P2.50mm_Horizontal; MPN 0022057035
J9: MOTOR3; Molex_SPOX_5268-03A_1x03_P2.50mm_Horizontal; MPN 0022057035
J10: MOTOR4; Molex_SPOX_5268-03A_1x03_P2.50mm_Horizontal; MPN 0022057035
J11: ENCODER1; Molex_SPOX_5268-04A_1x04_P2.50mm_Horizontal; MPN 0022057045
J12: ENCODER2; Molex_SPOX_5268-04A_1x04_P2.50mm_Horizontal; MPN 0022057045
J13: ENCODER3; Molex_SPOX_5268-04A_1x04_P2.50mm_Horizontal; MPN 0022057045
J14: ENCODER4; Molex_SPOX_5268-04A_1x04_P2.50mm_Horizontal; MPN 0022057045
R20: 330; R_0603_1608Metric; Tolerance 1%; MPN CRCW0603330RFKEA
R21: 10k; R_0603_1608Metric; Tolerance 1%; MPN ERJ-3EKF1002V
U10: 74AHCT1G125; SOT-353_SC-70-5; MPN SN74AHCT1G125DCKR

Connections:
+3V3: J11.1, J12.1, J13.1, J14.1; also elsewhere on the board
+5V_LED1: C44.1, J3.1, U10.5 (VCC); also elsewhere on the board
+5V_LED2: J4.1; also elsewhere on the board
+5V_LED3: J5.1; also elsewhere on the board
+5V_LED4: J6.1; also elsewhere on the board
GND: C44.2, J3.2, J4.2, J5.2, J6.2, J7.2, J8.2, J9.2, J10.2, J11.2, J12.2, J13.2, J14.2, R21.2, U10.1, U10.3 (GND); also elsewhere on the board
LED_DATA: R21.1, U10.2; also elsewhere on the board
LED_DIN: J3.3, R20.2
M1_DIR: J7.3; also elsewhere on the board
M1_ENC_A: J11.3; also elsewhere on the board
M1_ENC_B: J11.4; also elsewhere on the board
M1_PWM: J7.1; also elsewhere on the board
M2_DIR: J8.3; also elsewhere on the board
M2_ENC_A: J12.3; also elsewhere on the board
M2_ENC_B: J12.4; also elsewhere on the board
M2_PWM: J8.1; also elsewhere on the board
M3_DIR: J9.3; also elsewhere on the board
M3_ENC_A: J13.3; also elsewhere on the board
M3_ENC_B: J13.4; also elsewhere on the board
M3_PWM: J9.1; also elsewhere on the board
M4_DIR: J10.3; also elsewhere on the board
M4_ENC_A: J14.3; also elsewhere on the board
M4_ENC_B: J14.4; also elsewhere on the board
M4_PWM: J10.1; also elsewhere on the board
unnamed: R20.1, U10.4

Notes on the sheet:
01 / M1 - FRONT LEFT
06 / LED POWER + DATA PORTS
05 / LED DATA - 3.3 V TO 5 V
04 / M4 - REAR LEFT
3.3 V -> 5 V LED data; U10 always enabled (/OE = GND). U4 buck +5V_LED1 supplies U10 and LED1; common GND.
03 / M3 - REAR RIGHT
LED DATA: single chain; bar 1 DOUT -> bar 2 DIN -> bar 3 -> bar 4. Keep +5V_LED1..4 separate in the harness. All grounds are common.
Motor connectors: 3V3 PWM/DIR signals only. Encoder power and I/O: 3V3 only.
02 / M2 - FRONT RIGHT

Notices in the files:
parts and their libraries:
Geometry based on KiCad AMASS_XT60-M/F vertical footprints (CC-BY-SA-4.0 with KiCad exception); pin 1 reassigned to positive/square end, pin 2 to negative/bevelled end.
